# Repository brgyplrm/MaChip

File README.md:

# MaChip: RFID-Based Identification & Attendance System

**MaChip** is a modern office automation solution designed to streamline attendance tracking and access control in logistics hubs. By replacing manual logs with RFID/NFC technology and biometric verification, it ensures data integrity, prevents fraud, and complies with international shipping standards (CTPAT).

---

## 📋 Project Overview

Developed as a research-driven project at the **Polytechnic University of the Philippines, San Juan Campus**, MaChip leverages a mixed-method research design to reduce administrative burdens and eliminate "buddy punching."

### Core Objectives
*   **Security:** Adheres to the CIA (Confidentiality, Integrity, Availability) triad.
*   **Efficiency:** Automated payroll generation based on real-time attendance logs.
*   **Compliance:** Meets international security standards for logistics and forwarding.

---

## 🏗️ Project Structure

The project is split into a **React (Vite) Frontend** and a **Node.js (Express) Backend**, following modular and MVC architectural patterns.

### 💻 Frontend (`/frontend`)
Organized for scalability and clear separation of concerns.

| Directory/File | Description |
| :--- | :--- |
| `src/assets/` | Static assets: images, logos, fonts, and SVGs. |
| `src/components/` | Reusable UI components (Sidebar, Navbar, Table, Toast, Modals). |
| `src/pages/` | Route-specific views (Home, Payroll, User Management). |
| `src/utils/` | Shared helper logic: data formatters, constants, and export logic. |
| `src/hooks/` | Custom React hooks for shared logic. |
| `src/services/` | API interaction layer for centralized backend communication. |
| `src/context/` | Global state management (Auth, Theme). |
| `App.jsx` | Main application router and protected route definitions. |
| `Main.jsx` | Application entry point. |

#### Naming Conventions
*   **PascalCase:** Used for all JSX files (Pages and Components).
    *   *Example:* `PayrollManagement.jsx`, `DetailsPayroll.jsx`.
*   **camelCase:** Used for utility and helper files.
    *   *Example:* `datatableSource.jsx`, `formatUserId.js`.

---

### ⚙️ Backend (`/backend`)
Follows the **MVC (Model-View-Controller)** pattern for structured data flow.

| Directory | Description |
| :--- | :--- |
| `src/models/` | Sequelize blueprints for database tables (User, Attendance, Payroll). |
| `src/controllers/` | Business logic for processing requests and generating responses. |
| `src/routes/` | API endpoint definitions (RESTful). |
| `src/middleware/` | Request interceptors for authentication, security, and file uploads. |
| `src/config/` | Database and environment configurations. |
| `src/utils/` | Backend utilities (Holiday scrapers, system time management). |
| `app.js` | Main server initialization and middleware mounting. |
| `uploads/` | Local storage for user-uploaded files (Profile pics, documents). |

---

## 🛠️ Technical Stack

### Software
*   **Frontend:** React, Vite, Material UI (MUI), SCSS.
*   **Backend:** Node.js, Express.js.
*   **Database:** MySQL with Sequelize ORM.
*   **Testing:** Postman Collections (located in `.postman/`).

### Hardware (Scanner Unit)
*   **Microcontroller:** ESP32.
*   **RFID Module:** MFRC522 (13.56 MHz).
*   **Connectivity:** ENC28J60 Ethernet Module (Wired LAN for stability).
*   **Firmware:** Arduino C/C++.

---

## 🚀 Getting Started

### Prerequisites
*   **Node.js** (v16.x or higher)
*   **MySQL Server**
*   **Arduino IDE** (for hardware deployment)

### Installation & Setup

1.  **Clone the repository:**
    ```bash
    git clone https://github.com/yourusername/machip.git
    cd machip
    ```

2.  **Reset and Install Dependencies:**
    Runs the cleanup and installs all necessary packages for both frontend and backend.
    ```bash
    npm run reset
    ```

3.  **Environment Variables:**
    Configure your `.env` files in both the root and `backend/` directories with your MySQL credentials.

4.  **Run the Application:**
    Starts both the backend and frontend in development mode.
    ```bash
    npm run dev
    ```

---

## 👥 Authors
*   **Palermo, Borgy Misael K.** - Researcher
*   **Lapido, Jhanna Lou R.** - Researcher
*   **Pinto, Kathleen I.** - Researcher
*   **Tomas, Cydoel M.** - Researcher
*   **Morales, Trecia** - Researcher

---

## ⚖️ License
This project is developed for academic research purposes. Source code is provided under the **MIT License**.

> **Note:** This system is designed for local network use to ensure maximum security for corporate attendance data.

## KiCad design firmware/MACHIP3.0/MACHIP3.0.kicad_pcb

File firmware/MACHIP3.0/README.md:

# MACHIP 3.0 Hardware Terminal (PCB & Schematic)

This directory contains the official KiCad 8/10 hardware design files, production Gerbers, bill of materials (BOM), and assembly guides for the **MACHIP 3.0 Access Control Terminal**.

---

## Quick Navigation

- **KiCad Project File:** [`MACHIP3.0.kicad_pro`](MACHIP3.0.kicad_pro)
- **Schematic File:** [`MACHIP3.0.kicad_sch`](MACHIP3.0.kicad_sch)
- **PCB Layout File:** [`MACHIP3.0.kicad_pcb`](MACHIP3.0.kicad_pcb)
- **Production Gerbers (JLCPCB Ready):** [`MACHIP3.0_JLCPCB_READY.zip`](MACHIP3.0_JLCPCB_READY.zip)
- **Verified Component BOM (LCSC):** [`MACHIP3.0_JLCPCB_BOM_CORRECTED.csv`](MACHIP3.0_JLCPCB_BOM_CORRECTED.csv)
- **Hardware Assembly & Bring-Up Guide:** [`MACHIP3_HARDWARE_BRINGUP_AND_ASSEMBLY_GUIDE.md`](MACHIP3_HARDWARE_BRINGUP_AND_ASSEMBLY_GUIDE.md)
- **Pre-Fab Engineering Audit Report:** [`MACHIP3_PCB_LAYOUT_AUDIT_REPORT.md`](MACHIP3_PCB_LAYOUT_AUDIT_REPORT.md)

---

## How to Open on Your Laptop

### Option 1: In KiCad (Full Design & Editing)
1. Install **KiCad 8.0+** (or KiCad 10).
2. Clone this repository or download this folder.
3. Open KiCad $\to$ **File** $\to$ **Open Project** $\to$ Select `MACHIP3.0.kicad_pro`.
4. *Custom Footprints & Symbols:* The included `fp-lib-table`, `sym-lib-table`, and `machip_footprints.pretty/` will load all custom footprints automatically without library warnings.

### Option 2: In Web Browser (No Installation Needed!)
You can view the schematic and PCB interactively online:
1. Go to [kicanvas.org](https://kicanvas.org).
2. Drag and drop `MACHIP3.0.kicad_sch` or `MACHIP3.0.kicad_pcb` directly into your browser.

---

## Hardware Specifications

- **Controller:** ESP32-WROOM-32 (38-Pin DevKit Socket)
- **Operating Voltage:** 9.0V DC Regulated Input (5.5mm × 2.1mm Center-Positive Barrel Jack)
- **Onboard Regulators:**
  - `U1` (LM7805 TO-220 + Aluminum Heatsink): 5V System Bus
  - `U3` (RT9080-33GJ5 SOT-23-5): 3.3V Logic Rail (600mA Low-Dropout)
- **Peripherals Supported:**
  - `J2`: Inside MFRC522 RFID Reader (SPI, 7-Pin JST-XH)
  - `J3`: Outside MFRC522 RFID Reader (SPI, 7-Pin JST-XH)
  - `J4`: Outside ST7789 TFT Display (SPI, 9-Pin JST-XH)
  - `J5`: Inside ST7789 TFT Display (SPI, 9-Pin JST-XH)
  - `J6`: R307 Optical Fingerprint Sensor (UART, 4-Pin JST-XH)
  - `J7`: Active Buzzer Module (3-Pin JST-XH)
  - `J8`: 12V Door Strike / Maglock Relay Driver (3-Pin JST-XH)
- **Protection:**
  - Reverse Polarity: P-Channel MOSFET (`AO3401`) + Zener (`BZT52C10`)
  - Overcurrent: Resettable PTC Fuse (`RXEF110`, 1.1A Hold)
  - Overvoltage / Surge: Bidirectional TVS Diode (`SMBJ10CA`)
  - ESD Protection: Multichannel TVS Arrays (`ESDSRV05-4`) on peripheral lines
- **Dimensions:** $111.5\,\text{mm} \times 101.0\,\text{mm}$ (2-Layer FR-4, 1.6mm thickness, 1 oz copper)
- **Mounting:** 4× M3 Mounting Holes (`H1`–`H4`) with $>6.5\,\text{mm}$ annular clearance

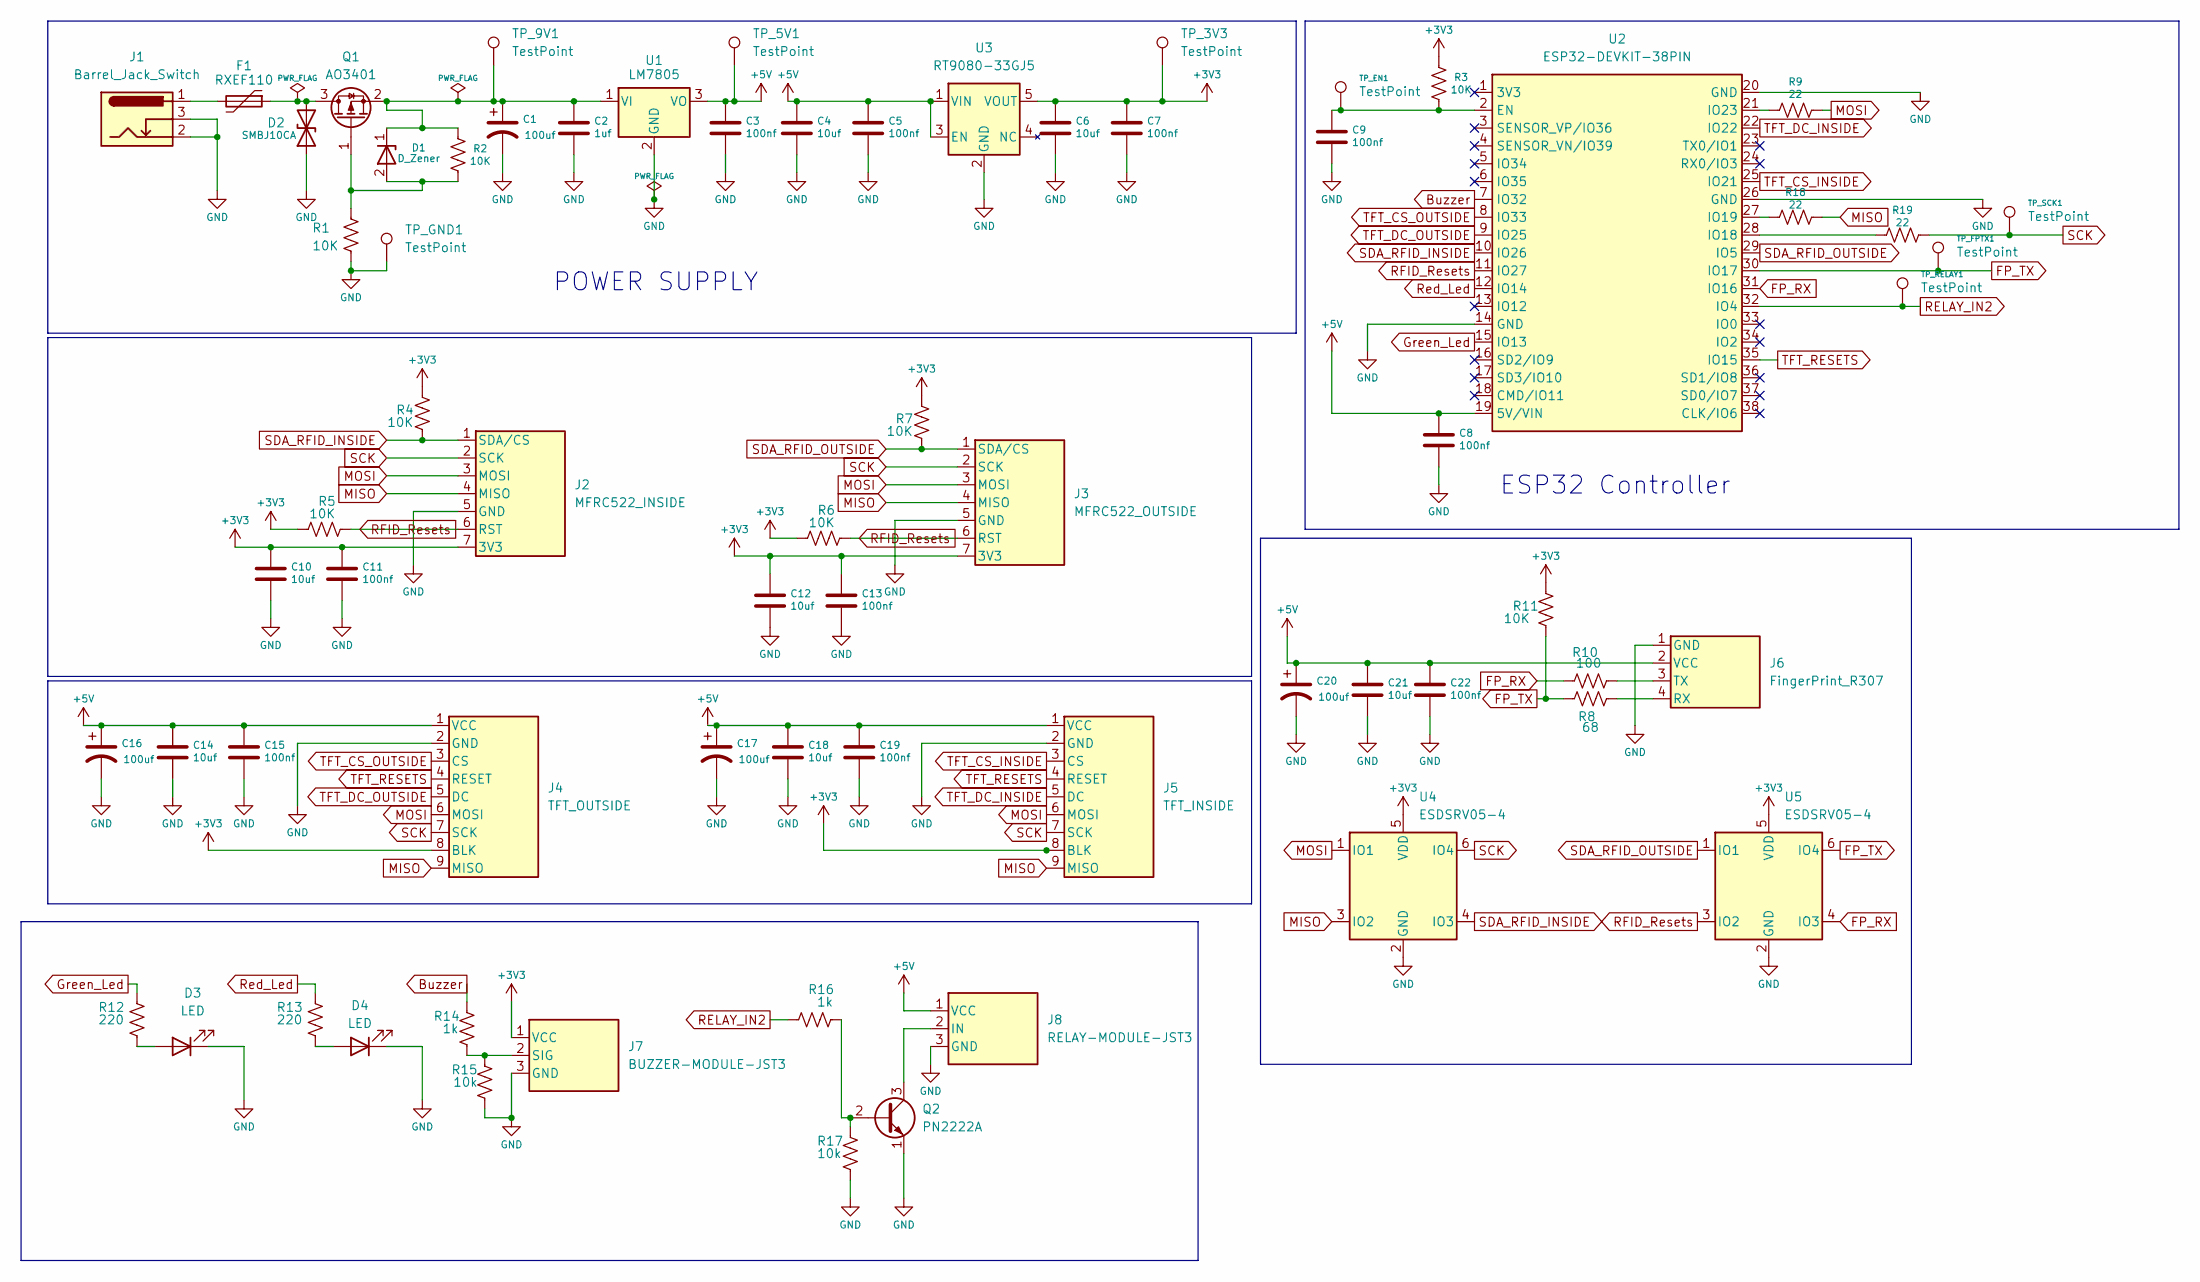
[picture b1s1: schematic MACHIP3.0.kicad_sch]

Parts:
C1, C16, C17, C20: 100uf; CP_Radial_D6.3mm_P2.50mm
C2: 1uf; C_Disc_D5.0mm_W2.5mm_P2.50mm
C3, C5, C7, C8, C9, C11, C13, C15, C19, C22: 100nf; C_Disc_D5.0mm_W2.5mm_P2.50mm
C4, C6, C10, C12, C14, C18, C21: 10uf; CP_Radial_D5.0mm_P2.50mm
D1: D_Zener; D_SOD-123
D2: SMBJ10CA; D_SMB
D3, D4: LED; JST_XH_B2B-XH-A_1x02_P2.50mm_Vertical
F1: RXEF110; Fuse_Bourns_MF-RHT100
J1: Barrel_Jack_Switch; BarrelJack_Horizontal
J2: MFRC522_INSIDE; JST_XH_B7B-XH-A_1x07_P2.50mm_Vertical
J3: MFRC522_OUTSIDE; JST_XH_B7B-XH-A_1x07_P2.50mm_Vertical
J4: TFT_OUTSIDE; JST_XH_B9B-XH-A_1x09_P2.50mm_Vertical
J5: TFT_INSIDE; JST_XH_B9B-XH-A_1x09_P2.50mm_Vertical
J6: FingerPrint_R307; JST_XH_B4B-XH-A_1x04_P2.50mm_Vertical
J7: BUZZER-MODULE-JST3; JST_XH_B3B-XH-A_1x03_P2.50mm_Vertical
J8: RELAY-MODULE-JST3; JST_XH_B3B-XH-A_1x03_P2.50mm_Vertical
Q1: AO3401; SOT-23
Q2: PN2222A; TO-92_Inline
R1, R2, R3, R4, R5, R6, R7, R11: 10K; R_Axial_DIN0207_L6.3mm_D2.5mm_P10.16mm_Horizontal
R8: 68; R_Axial_DIN0207_L6.3mm_D2.5mm_P10.16mm_Horizontal
R9, R18, R19: 22; R_Axial_DIN0207_L6.3mm_D2.5mm_P10.16mm_Horizontal
R10: 100; R_Axial_DIN0207_L6.3mm_D2.5mm_P10.16mm_Horizontal
R12, R13: 220; R_Axial_DIN0207_L6.3mm_D2.5mm_P10.16mm_Horizontal
R14, R16: 1k; R_Axial_DIN0207_L6.3mm_D2.5mm_P10.16mm_Horizontal
R15, R17: 10k; R_Axial_DIN0207_L6.3mm_D2.5mm_P10.16mm_Horizontal
TP_3V3, TP_5V1, TP_9V1: TestPoint; TestPoint_Pad_D1.5mm
TP_EN1: TestPoint; TestPoint_Pad_D1.5mm
TP_FPTX1: TestPoint; TestPoint_Pad_D1.5mm
TP_GND1: TestPoint; TestPoint_Loop_D2.50mm_Drill1.0mm
TP_RELAY1: TestPoint; TestPoint_Pad_D1.5mm
TP_SCK1: TestPoint; TestPoint_Pad_D1.5mm
U1: LM7805; TO-220-3_Vertical
U2: ESP32-DEVKIT-38PIN
U3: RT9080-33GJ5; SOT-23-5; LCSC C91443
U4, U5: ESDSRV05-4; SOT-23-6

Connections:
+3V3: C6.1, C7.1, C10.1, C11.1, C12.1, C13.1, J2.7 (3V3), J3.7 (3V3), J4.8 (BLK), J5.8 (BLK), J7.1 (VCC), R3.1, R4.1, R5.2, R6.2, R7.1, R11.1, TP_3V3.1 (1_1), U3.5 (VOUT), U4.5 (VDD), U5.5 (VDD)
+5V: C3.1, C4.1, C5.1, C8.1, C14.1, C15.1, C16.1, C17.1, C18.1, C19.1, C20.1, C21.1, C22.1, J4.1 (VCC), J5.1 (VCC), J6.2 (VCC), J8.1 (VCC), TP_5V1.1 (1_1), U1.3 (VO), U2.19 (5V/VIN), U3.1 (VIN), U3.3 (EN)
Buzzer: R14.1, U2.7 (IO32)
FP_RX: R10.2, U2.31 (IO16), U5.4 (IO3)
FP_TX: R8.2, R11.2, TP_FPTX1.1 (1_1), U2.30 (IO17), U5.6 (IO4)
GND: C1.2, C2.2, C3.2, C4.2, C5.2, C6.2, C7.2, C8.2, C9.2, C10.2, C11.2, C12.2, C13.2, C14.2, C15.2, C16.2, C17.2, C18.2, C19.2, C20.2, C21.2, C22.2, D2.1 (A1), D3.1 (K), D4.1 (K), J1.2, J1.3, J2.5 (GND), J3.5 (GND), J4.2 (GND), J5.2 (GND), J6.1 (GND), J7.3 (GND), J8.3 (GND), Q2.1 (E), R1.2, R15.2, R17.2, TP_GND1.1 (1_1), U1.2 (GND), U2.14 (GND), U2.20 (GND), U2.26 (GND), U3.2 (GND), U4.2 (GND), U5.2 (GND)
Green_Led: R12.1, U2.15 (IO13)
MISO: J2.4 (MISO), J3.4 (MISO), J4.9 (MISO), J5.9 (MISO), R18.2, U4.3 (IO2)
MOSI: J2.3 (MOSI), J3.3 (MOSI), J4.6 (MOSI), J5.6 (MOSI), R9.2, U4.1 (IO1)
unnamed: D1.2 (A), Q1.1 (G), R1.1, R2.2
unnamed: C1.1, C2.1, D1.1 (K), Q1.2 (S), R2.1, TP_9V1.1 (1_1), U1.1 (VI)
unnamed: D2.2 (A2), F1.1, Q1.3 (D)
unnamed: D3.2 (A), R12.2
unnamed: D4.2 (A), R13.2
unnamed: F1.2, J1.1
unnamed: J6.4 (RX), R8.1
unnamed: J6.3 (TX), R10.1
unnamed: J7.2 (SIG), R14.2, R15.1
unnamed: J8.2 (IN), Q2.3 (C)
unnamed: Q2.2 (B), R16.1, R17.1
unnamed: C9.1, R3.2, TP_EN1.1 (1_1), U2.2 (EN)
unnamed: R19.1, U2.28 (IO18)
unnamed: R18.1, U2.27 (IO19)
unnamed: R9.1, U2.21 (IO23)
RELAY_IN2: R16.2, TP_RELAY1.1 (1_1), U2.32 (IO4)
RFID_Resets: J2.6 (RST), J3.6 (RST), R5.1, R6.1, U2.11 (IO27), U5.3 (IO2)
Red_Led: R13.1, U2.12 (IO14)
SCK: J2.2 (SCK), J3.2 (SCK), J4.7 (SCK), J5.7 (SCK), R19.2, TP_SCK1.1 (1_1), U4.6 (IO4)
SDA_RFID_INSIDE: J2.1 (SDA/CS), R4.2, U2.10 (IO26), U4.4 (IO3)
SDA_RFID_OUTSIDE: J3.1 (SDA/CS), R7.2, U2.29 (IO5), U5.1 (IO1)
TFT_CS_INSIDE: J5.3 (CS), U2.25 (IO21)
TFT_CS_OUTSIDE: J4.3 (CS), U2.8 (IO33)
TFT_DC_INSIDE: J5.5 (DC), U2.22 (IO22)
TFT_DC_OUTSIDE: J4.5 (DC), U2.9 (IO25)
TFT_RESETS: J4.4 (RESET), J5.4 (RESET), U2.35 (IO15)

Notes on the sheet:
POWER SUPPLY
ESP32 Controller

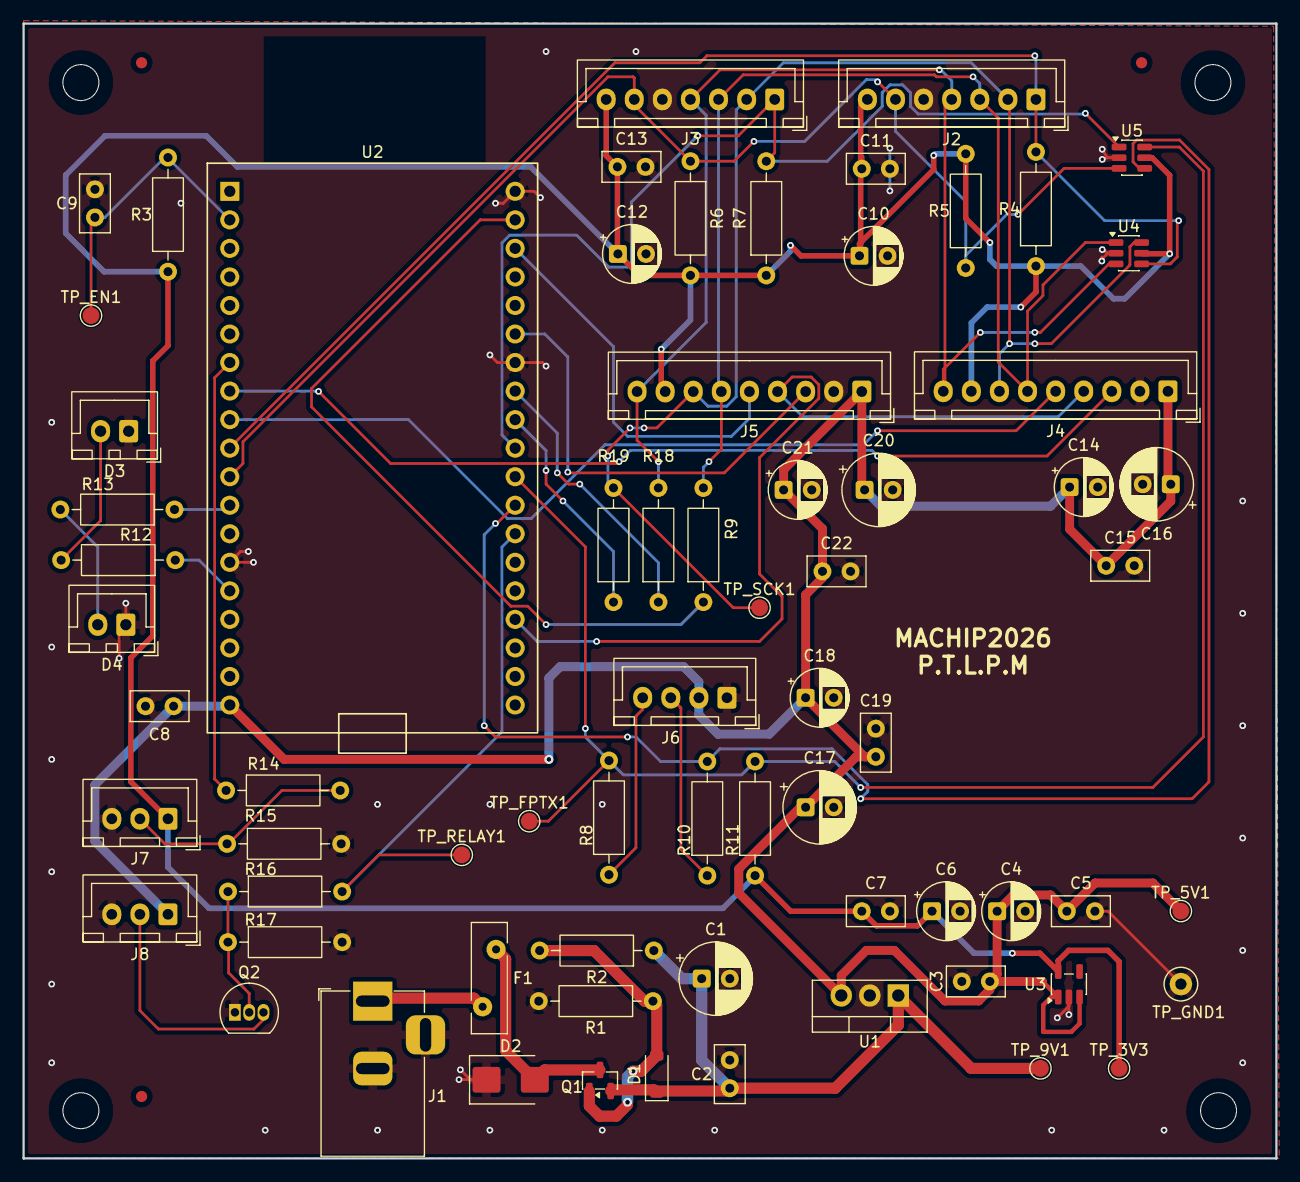
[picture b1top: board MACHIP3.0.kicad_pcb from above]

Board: 2 copper layers, 111.5 x 101.0 mm, 76 parts (0 on the bottom side), 35 nets.

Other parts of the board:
FID1, FID2, FID3: Fiducial_1mm_Mask2mm
H1, H2, H3, H4: 3.2mm_M3; MountingHole_3.2mm_M3

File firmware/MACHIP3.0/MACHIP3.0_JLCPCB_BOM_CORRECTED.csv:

Comment,Designator,Footprint,LCSC Part #,Quantity,Manufacturer Part,Description
10uF,"C4,C6,C10,C12,C14,C18,C21",Capacitor_THT:CP_Radial_D5.0mm_P2.50mm,C334526,7,Radial 10uF 25V/50V,10uF 50V Radial Electrolytic D5.0mm P2.5mm
100uF,"C1,C16,C17,C20",Capacitor_THT:CP_Radial_D6.3mm_P2.50mm,C48970442,4,RYHG35V100UF6*8,100uF 35V Radial Electrolytic D6.3mm P2.5mm
100nF,"C3,C5,C7,C8,C9,C11,C13,C15,C19,C22",Capacitor_THT:C_Disc_D5.0mm_W2.5mm_P2.50mm,C1004,10,Ceramic 100nF 50V,100nF (0.1uF) 50V Ceramic Disc Capacitor P2.5mm
1uF,C2,Capacitor_THT:C_Disc_D5.0mm_W2.5mm_P2.50mm,C14663,1,Ceramic 1uF 50V,1uF 50V Ceramic Disc Capacitor P2.5mm
Barrel_Jack_Switch,J1,Connector_BarrelJack:BarrelJack_Horizontal,C42376853,1,DC-005D-1-2.0-PU-B-SP,DC Power Jack 2.0mm Center Pin Through-Hole
LED,D4,Connector_JST:JST_XH_B2B-XH-A_1x02_P2.50mm_Vertical,C157925,1,B2B-XH-A(LF)(SN),JST-XH 2-Pin 2.50mm Vertical Shrouded Header (Green LED Cable)
LED,D3,Connector_JST:JST_XH_B2B-XH-A_1x02_P2.50mm_Vertical,C157925,1,B2B-XH-A(LF)(SN),JST-XH 2-Pin 2.50mm Vertical Shrouded Header (Red LED Cable)
BUZZER-MODULE-JST3,J7,Connector_JST:JST_XH_B3B-XH-A_1x03_P2.50mm_Vertical,C157926,1,B3B-XH-A(LF)(SN),JST-XH 3-Pin 2.50mm Vertical Shrouded Header
RELAY-MODULE-JST3,J8,Connector_JST:JST_XH_B3B-XH-A_1x03_P2.50mm_Vertical,C157926,1,B3B-XH-A(LF)(SN),JST-XH 3-Pin 2.50mm Vertical Shrouded Header
FingerPrint_R307,J6,Connector_JST:JST_XH_B4B-XH-A_1x04_P2.50mm_Vertical,C157927,1,B4B-XH-A(LF)(SN),JST-XH 4-Pin 2.50mm Vertical Shrouded Header
MFRC522_INSIDE,J2,Connector_JST:JST_XH_B7B-XH-A_1x07_P2.50mm_Vertical,C157930,1,B7B-XH-A(LF)(SN),JST-XH 7-Pin 2.50mm Vertical Shrouded Header
MFRC522_OUTSIDE,J3,Connector_JST:JST_XH_B7B-XH-A_1x07_P2.50mm_Vertical,C157930,1,B7B-XH-A(LF)(SN),JST-XH 7-Pin 2.50mm Vertical Shrouded Header
TFT_INSIDE,J5,Connector_JST:JST_XH_B9B-XH-A_1x09_P2.50mm_Vertical,C157932,1,B9B-XH-A(LF)(SN),JST-XH 9-Pin 2.50mm Vertical Shrouded Header
TFT_OUTSIDE,J4,Connector_JST:JST_XH_B9B-XH-A_1x09_P2.50mm_Vertical,C157932,1,B9B-XH-A(LF)(SN),JST-XH 9-Pin 2.50mm Vertical Shrouded Header
SMBJ10CA,D2,Diode_SMD:D_SMB,C49066943,1,SMBJ10CA,TVS Diode 10V Bidirectional SMB (DO-214AA)
D_Zener,D1,Diode_SMD:D_SOD-123,C20611960,1,BZT52C10,Zener Diode 10V 500mW SOD-123
RXEF110,F1,Fuse:Fuse_Bourns_MF-RHT100,C434722,1,RXEF110-2,PTC Resettable Fuse 1.1A Hold Radial 5.08mm
AO3401,Q1,Package_TO_SOT_SMD:SOT-23,C2847031,1,AO3401MI-MS,P-Channel MOSFET -30V -4.2A SOT-23
RT9080-33GJ5,U3,Package_TO_SOT_SMD:SOT-23-5,C841192,1,RT9080-33GJ5,LDO Regulator 3.3V 600mA SOT-23-5
ESDSRV05-4,"U4,U5",Package_TO_SOT_SMD:SOT-23-6,C2920029,2,ESDSRV05-4H,TVS Diode Array 5V SOT-23-6
LM7805,U1,Package_TO_SOT_THT:TO-220-3_Vertical,C71107,1,LM7805L-TF3-T,Linear Regulator 5V 1.5A TO-220F-3
PN2222A,Q2,Package_TO_SOT_THT:TO-92_Inline,C118536,1,2N2222A,NPN Bipolar Transistor 40V 0.8A TO-92
100,R10,Resistor_THT:R_Axial_DIN0207_L6.3mm_D2.5mm_P10.16mm_Horizontal,Through-Hole,1,100 Ohm 1/4W 1%,100 Ohm 0.25W Metal Film Resistor Axial 10mm
10k,"R1,R2,R3,R4,R5,R6,R7,R11,R15,R17",Resistor_THT:R_Axial_DIN0207_L6.3mm_D2.5mm_P10.16mm_Horizontal,Through-Hole,10,10k Ohm 1/4W 1%,10k Ohm 0.25W Metal Film Resistor Axial 10mm
1k,"R14,R16",Resistor_THT:R_Axial_DIN0207_L6.3mm_D2.5mm_P10.16mm_Horizontal,Through-Hole,2,1k Ohm 1/4W 1%,1k Ohm 0.25W Metal Film Resistor Axial 10mm
22,"R9,R18,R19",Resistor_THT:R_Axial_DIN0207_L6.3mm_D2.5mm_P10.16mm_Horizontal,Through-Hole,3,22 Ohm 1/4W 1%,22 Ohm 0.25W Metal Film Resistor Axial 10mm
220,"R12,R13",Resistor_THT:R_Axial_DIN0207_L6.3mm_D2.5mm_P10.16mm_Horizontal,Through-Hole,2,220 Ohm 1/4W 1%,220 Ohm 0.25W Metal Film Resistor Axial 10mm
68,R8,Resistor_THT:R_Axial_DIN0207_L6.3mm_D2.5mm_P10.16mm_Horizontal,Through-Hole,1,68 Ohm 1/4W 1%,68 Ohm 0.25W Metal Film Resistor Axial 10mm
ESP32-DEVKIT-38PIN,U2,machip_footprints:ESP32-DEVKIT-38PIN,C319202,2,2.54mm 1*19P Female Header (x2),19-Pin 2.54mm Female Header Socket (Need 2 pcs)

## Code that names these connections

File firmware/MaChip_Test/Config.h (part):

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#define MIFARE_SECTOR_TRAILER_BLOCK 7

// ── HARDWARE LAYER PIN DEFINITIONS (MACHIP 3.0 PCB CERTIFIED) ───
#define GREEN_LED          13    // Physical UI Green Indicator (D3 via R12)
#define RED_LED            14    // Physical UI Red Indicator (D4 via R13)
#define SOLENOID_PIN       4     // Relay Control (J8 Pin 2 via Q2 NPN Open-Collector) - HIGH = UNLOCK (Triggers Relay), LOW = LOCK (Rest)
#define BUZZER             32    // PWM Audio Feedback Pin (J7 Pin 2 via R14/R15)
#define FP_RX              16    // ESP32 UART2 RX <- R307S TX (J6 Pin 3)
#define FP_TX              17    // ESP32 UART2 TX -> R307S RX (J6 Pin 4 via R10)

// SPI Bus Mappings for Dual MFRC522 Modules & Displays
#define TFT_SCK            18    // Shared SPI Clock (SCK)
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#define SS_PIN_OUT         5     // Back Door Select Pin (J2 Pin 1, GPIO 5)

// Master Hardware Reset Pins on MAChip 3.0 PCB
#define RFID_RESET_PIN     27    // Net "RFID_Resets" (GPIO 27) drives J2, J3 (Dual MFRC522)
#define TFT_RESET_PIN      15    // Net "TFT_RESETS" (GPIO 15) drives J4, J5 (Dual ST7789)
#define HARDWARE_RESET_PIN RFID_RESET_PIN
#define RST_PIN_IN         RFID_RESET_PIN  // J2 RFID Inside Reset
#define RST_PIN_OUT        RFID_RESET_PIN  // J3 RFID Outside Reset
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#define TFT_RST            TFT_RESET_PIN // J4 Dedicated Reset (GPIO 15)

// Back Terminal: 2.4" ST7789 SPI TFT (J5 Inside Display)
#define TFT_CS_INSIDE      21    // J5 Inside Display Chip Select (GPIO 21)
#define TFT_DC_INSIDE      22    // J5 Inside Display Data/Command (GPIO 22)
#define TFT_RST_INSIDE     TFT_RESET_PIN // J5 Dedicated Reset (GPIO 15)

// Display Configuration Flags
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#define SCREEN_HEIGHT      64

// ── TIMERS & BUZZER ACOUSTIC PROFILES ─────────────────────────────
#define BUZZER_IS_ACTIVE   false // User confirmed: PASSIVE buzzer (requires PWM oscillation)
#define BUZZER_FREQ        2093  // Modern, pleasant musical tone (C7 note, non-piercing)
#define BUZZER_RES         8
#define DEFAULT_SOLENOID_DURATION  3000
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
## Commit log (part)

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2026-02-15 Refactor code structure for improved readability and maintainability
2026-02-15 feat: add to-regex-range package for regex range matching
    feat: add touch package for file touch functionality with CLI and API
    feat: implement undefsafe package for safe object property access
    chore: add database configuration and Sequelize connection setup
    feat: create attendance and user models with initial structure
    feat: add attendance routes for handling attendance-related requests
2026-02-21 feat: add platform-specific scripts for semver and uuid binaries
2026-02-24 feat: implement user ID generation and RFID functionality; update user registration form and validation
2026-02-24 Integrated backend folder from machip-backend branch
2026-02-24 refactor: update user input fields and improve form handling in New and Edit components
2026-02-24 feat: wrap Dashboard link in Sidebar component with Link for navigation; add gap to list item styles
2026-02-25 change the user_Num incrementing in the datatable.jsx in the User list page
2026-02-25 feat: implement user authentication flow with login and logout functionality; add notifications and settings pages
2026-03-01 feat: enhance navigation with breadcrumbs and add search functionality to logs
2026-03-01 fix the statuses, added paranoid table for soft deletion, and fix login page and authentication
2026-03-10 Switch to TIDB mysql to POSTGRES
2026-03-14 Update package-lock.json dependencies and add Payroll Management component
2026-03-15 fix(employee-home): correct stylesheet import for EmployeeHome component
2026-03-15 Fetch the requesting system
2026-03-16 feat: implement file upload system for leave requests
2026-03-16 feat: implement user requests and calendar functionality with routing and dynamic details
2026-03-16 feat(payroll): sync unpaid leaves with total absences and allow manual adjustment
    - Updates `absenceDays` automatically when `unpaidLeaveDays` is changed
    in the frontend.
    - Keeps `absenceDays` editable for manual overrides by admin/finance.
    - Calculates net days worked as `totalScheduledDays - absenceDays`.
    - Fixes backend `updatePayroll` to correctly persist manually updated
    absence days.
2026-03-27 latest changes (Mock2)
2026-03-28 feat(payroll): restructure payroll routes and components; add new modals for period creation and processing
2026-03-29 fix: resolve reference errors and improve payroll generation persistence
    - Fix ReferenceError for User in request.model.js by resolving circular
    dependencies
    - Fix ReferenceError for sequelize in system.controller.js and
    fetchActive in frontend
    - Implement live "Potential Pay" and employee count estimates for Draft
    periods
2026-04-01 feat: Implement access logs page and modal for password reset functionality
2026-04-01 feat: Redesign Notifications page with improved layout and enhanced user interaction
2026-04-02 fix: resolve rendering issues and complete calendar CRUD functionality - Fix Recharts `ResponsiveContainer` sizing error by adding `min-width: 0` to chart containers. - Resolve Vite transform and MIM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
2026-04-06 feat: enhance backend communication and response handling in RFID scanning
2026-04-08 QA SUM SHIT
2026-04-10 fix: refine loop structure for RFID scanning logic
2026-04-10 feat: add DTR PDF generation and integrate with payroll email
    - Added Puppeteer as a dependency for generating DTR PDFs.
    - Created a new utility function `generateDTRPDF` to build and generate DTR PDFs.
    - Updated `payroll.controller.js` to include DTR PDF generation in batch payroll and release payroll processes.
    - Refactored `attendance.controller.js` to extract attendance report logic into a separate internal function.
    - Modified attendance report response structure to include `hoursWorked` instead of `hours_worked`.
    - Updated frontend components to reflect changes in attendance data structure and improve report filtering.
2026-04-16 feat: Improve responsive design and layout adjustments across employeeHome, login, and userRequests pages
2026-04-20 fixing ensureabsentmarked the logs run every 10 instead of 5:30PM and fix the mock time
2026-04-27 packages
2026-04-28 feat: add Breadcrumbs, CardForm, and Sidebar components; implement Tailwind CSS for styling
    - Introduced Breadcrumbs component for navigation.
    - Created CardForm component for user login.
    - Developed Sidebar component with user profile and navigation links.
    - Updated package.json to include Tailwind CSS and PostCSS dependencies.
    - Implemented Home page with dashboard stats and notifications.
2026-04-28 deleted page transition
2026-04-29 feat: Fix the DTR Generator Fix the Payslips
2026-04-30 fix: ensure payroll deduction integrity and persistent withholding tax template
    - Added 'tax_Share' to User model and manual migrations to allow
    persistent storage of withholding tax.
    - Updated payroll calculation logic to use saved 'tax_Share' from user
    templates instead of a hardcoded zero.
    - Fixed 'getPayrollReport' and retrieval endpoints to join
    deduction/earning tables, ensuring all data is
2026-05-01 feat: Enhance Single page with shadcn/ui components and loading states
2026-05-01 Refactor UI components across multiple pages for consistency and improved styling
    - Updated Edit page to use shadcn/ui components for form inputs and buttons, enhancing the user experience.
    - Modified EmployeeCalendar, EmployeeHome, Notifications, Profile, Settings, and UserRequests pages to standardize padding and layout.
    - Improved card components in EmployeeCalendar and UserRequests for better visual hierarchy.
    - Enhanced RequestDetails page with a more structured layout using cards for request information and review details.
    - Adjusted button styles and hover effects for better accessibility and user interaction.
2026-05-02 feat: implement cash advance management and attendance backfill logic
    Backend:
    - Payroll: Added 'Payroll_Cash_Advances' ledger table and model with manual migration.
    - Logic: Fixed bug in payroll calculation where ledger overrides were being ignored.
    - Sync: Integrated automatic sync between cash advance ledger and User compensation data.
    - Lifecycle: Added automatic reset of User.advances_Amnt upon payroll release.
    - Attendance: Implemented period-restricted backfill for missing absences at startup and daily 4:00 AM.
2026-05-03 feat: add loading screen component to enhance user experience during login
2026-05-06 - version napaltan ng di ko alam
2026-05-07 feat: Implement multi-step registration form with dynamic inputs and validation
    - Added a stepper for user registration with three steps: Personal Info, Employment & Payroll, and Security.
    - Grouped form fields logically for each step and added validation for required fields.
    - Integrated bank details section with a dropdown for Philippine banks and account information.
    - Enhanced user experience with dynamic input rendering and visibility toggles for sensitive fields.
    - Updated CSV template for batch upload to include new fields.
2026-05-11 Refactor dashboard cards to update background colors and text styles for better visibility; add new script to check user columns in the database.
2026-05-13 feat: enhance Maxicare HMO, automate gov deductions, and refine RBAC
    - **Maxicare HMO:** Implemented per-cycle configuration for premiums, terms, and start dates using JSONB storage. Fixed date overlap bugs with period-aware protection and added row-level table manage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
    - **Gov Deductions:** Automated SSS, PhilHealth, and HDMF calculations based on daily rates in both frontend (real-time) and backend. Added a contribution breakdown table to user profiles.
    - **RBAC & Navigation:** Expanded log access to accountants and strictly separated management/employee views in the sidebar and routing. Standardized year dropdowns module-wide.
    - **Data Integrity:** Hardened CSV uploads with unique Temp
2026-05-13 fix the acccess logs
2026-05-14 Fix the Maxicare history page.
2026-05-15 Add SCSS styles for various pages including payslip, profile, register, request details, settings, single view, and user requests
    - Created payslip.scss for styling the payslip page with responsive design and skeleton loading states.
    - Added profile.scss for user profile layout, including responsive adjustments and form styling.
    - Introduced register.scss for the registration page with form styling and button interactions.
    - Developed requestDetails.scss for displaying request details with a structured layout and timeline styles.
    - Implemented settings.scss for user settings page with responsive design and toggle switches.
    - Created single.scss for a detailed view layout with card styles and
2026-05-18 Refactor RFID and Fingerprint Scanning Logic
    - Updated formatUserId function to include MACJ- prefix.
    - Refactored handleScanRFID and handleScanFingerprint functions to improve readability and error handling.
    - Moved session management logic into dedicated close functions for better modularity.
    - Added auto-fetch for next user ID on component mount in New.jsx.
    - Enhanced error handling during scanning processes.
    - Cleaned up unused code and consolidated session management for both RFID and fingerprint modals.
2026-05-19 Added the shift configuration for the employee with consistent link to the settings for maintenance
2026-05-20 Add the Thirteenth Monthy Pay
2026-05-21 Fix the System Settings
2026-05-24 feat(payroll): add periodId to payroll details link in PayrollPeriod component
    fix(maxicare): validate saved dates and ensure proper date generation logic
    feat(payslip): add year-to-date summary section in Payslip component
    refactor(logs): enhance filtering logic and statistics calculation in Logs component
    delete(tests): remove outdated test_all_attendance.js file
    feat(migrations): ensure logged statuses and attendance statuses are seeded correctly
    feat(migrations): seed user rates with updated daily rates for specific users
2026-05-26 feat(payroll): add Loan Details page and integrate with Loan Management
2026-05-26 feat(settings): enhance tabbed navigation in Settings page for better layout feat(eastwestLoan): improve loan history display with empty state and refined header feat(sidebar): add settings dropdown 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
2026-05-27 feat(Sidebar): add label for attendance edit route in sidebar
2026-05-27 feat: Enhance loan request functionality for Pag-IBIG loans
    - Added new fields for Pag-IBIG loans in EditRequestModal and UserRequests components.
    - Implemented auto-calculation for monthly amortization based on loan amount and term for Pag-IBIG Multi-Purpose and Calamity Loans.
    - Updated loan approval date handling to calculate amortization start month based on agency type.
    - Enhanced LoanDetails and AdminRequests components to display new loan fields including Pag-IBIG TAV and calamity area.
    - Created backend migration script to add missing columns in Loan_Request table.
    - Added utility scripts for checking database constraints, enums, and inserting test data for cash advances.
2026-05-29 feat: add employee payslip, payroll computation details, and thirteenth month details pages
    - Implemented EmployeePayslip component to display individual payslip information.
    - Created PayrollComputationDetails component for detailed breakdown of earnings and deductions.
    - Added ThirteenthMonthDetails component to show 13th month pay computation and history.
    - Enhanced error handling and loading states for better user experience.
    - Included currency formatting and responsive design for improved UI.
2026-05-29 feat: improve currency formatting to ensure non-negative values in payroll computations and PDF generation
